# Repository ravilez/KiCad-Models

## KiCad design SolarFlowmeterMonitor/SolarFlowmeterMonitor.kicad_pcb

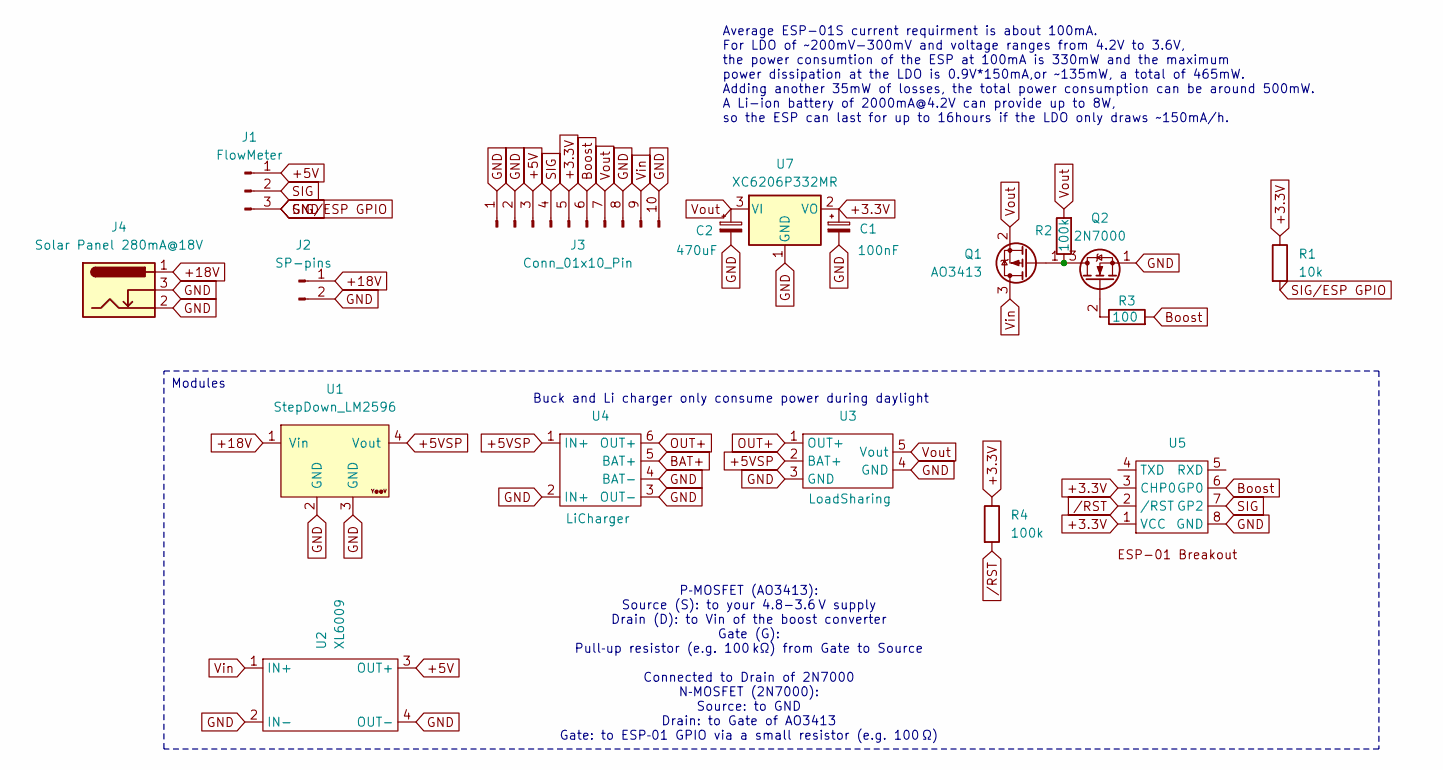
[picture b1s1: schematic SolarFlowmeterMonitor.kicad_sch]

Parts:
C1: 100nF; C_1210_3225Metric_Pad1.33x2.70mm_HandSolder
C2: 470uF; CP_Elec_10x10.5
J1: FlowMeter; PinHeader_1x03_P2.54mm_Vertical
J2: SP-pins; PinSocket_1x02_P2.54mm_Vertical
J3: Conn_01x10_Pin
J4: Solar Panel 280mA@18V; BarrelJack_Horizontal
Q1: AO3413; SOT-23
Q2: 2N7000; TO-92_Inline
R1: 10k; R_1210_3225Metric_Pad1.30x2.65mm_HandSolder
R2, R4: 100k; R_1210_3225Metric_Pad1.30x2.65mm_HandSolder
R3: 100; R_1210_3225Metric_Pad1.30x2.65mm_HandSolder
U1: StepDown_LM2596; YAAJ_DCDC_StepDown_LM2596
U2: XL6009; XL6009_module_TH
U3: LoadSharing; LiPO_SharePower
U4: LiCharger; LiCharger-03962
U5: ESP01-Breakout
U7: XC6206P332MR; SOT-23-3

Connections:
+3.3V: C1.1, J3.5, R1.1, R4.1, U5.1 (VCC), U5.3 (CHP0), U7.2 (VO)
+5V: J1.1, J3.3, U2.3 (OUT+)
+5VSP: U1.4 (Vout), U3.2 (BAT+), U4.1 (IN+)
+18V: J2.1, J4.1, U1.1 (Vin)
BAT+: U4.5 (BAT+)
Boost: J3.6, R3.2, U5.6 (GP0)
GND: C1.2, C2.2, J1.3, J2.2, J3.1, J3.2, J3.8, J3.10, J4.2, J4.3, Q2.1 (S), R1.2, U1.2 (GND), U1.3 (GND), U2.2 (IN-), U2.4 (OUT-), U3.3 (GND), U3.4 (GND), U4.2 (IN+), U4.3 (OUT-), U4.4 (BAT-), U5.8 (GND), U7.1 (GND)
unnamed: Q1.1 (G), Q2.3 (D), R2.1
unnamed: Q2.2 (G), R3.1
OUT+: U3.1 (OUT+), U4.6 (OUT+)
SIG: J1.2, J3.4, U5.7 (GP2)
Vin: J3.9, Q1.3 (D), U2.1 (IN+)
Vout: C2.1, J3.7, Q1.2 (S), R2.2, U3.5 (Vout), U7.3 (VI)
/RST: R4.2, U5.2 (/RST)

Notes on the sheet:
Average ESP-01S current requirment is about 100mA. For LDO of ~200mV-300mV and voltage ranges from 4.2V to 3.6V, the power consumtion of the ESP at 100mA is 330mW and the maximum power dissipation at the LDO is 0.9V*150mA,or ~135mW, a total of 465mW. Adding another 35mW of losses, the total power c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
Buck and Li charger only consume power during daylight
P‑MOSFET (AO3413): Source (S): to your 4.8-3.6 V supply Drain (D): to Vin of the boost converter Gate (G): Pull‑up resistor (e.g. 100 kΩ) from Gate to Source Connected to Drain of 2N7000 N‑MOSFET (2N7000): Source: to GND Drain: to Gate of AO3413 Gate: to ESP‑01 GPIO via a small resistor (e.g. 100 Ω)
Modules

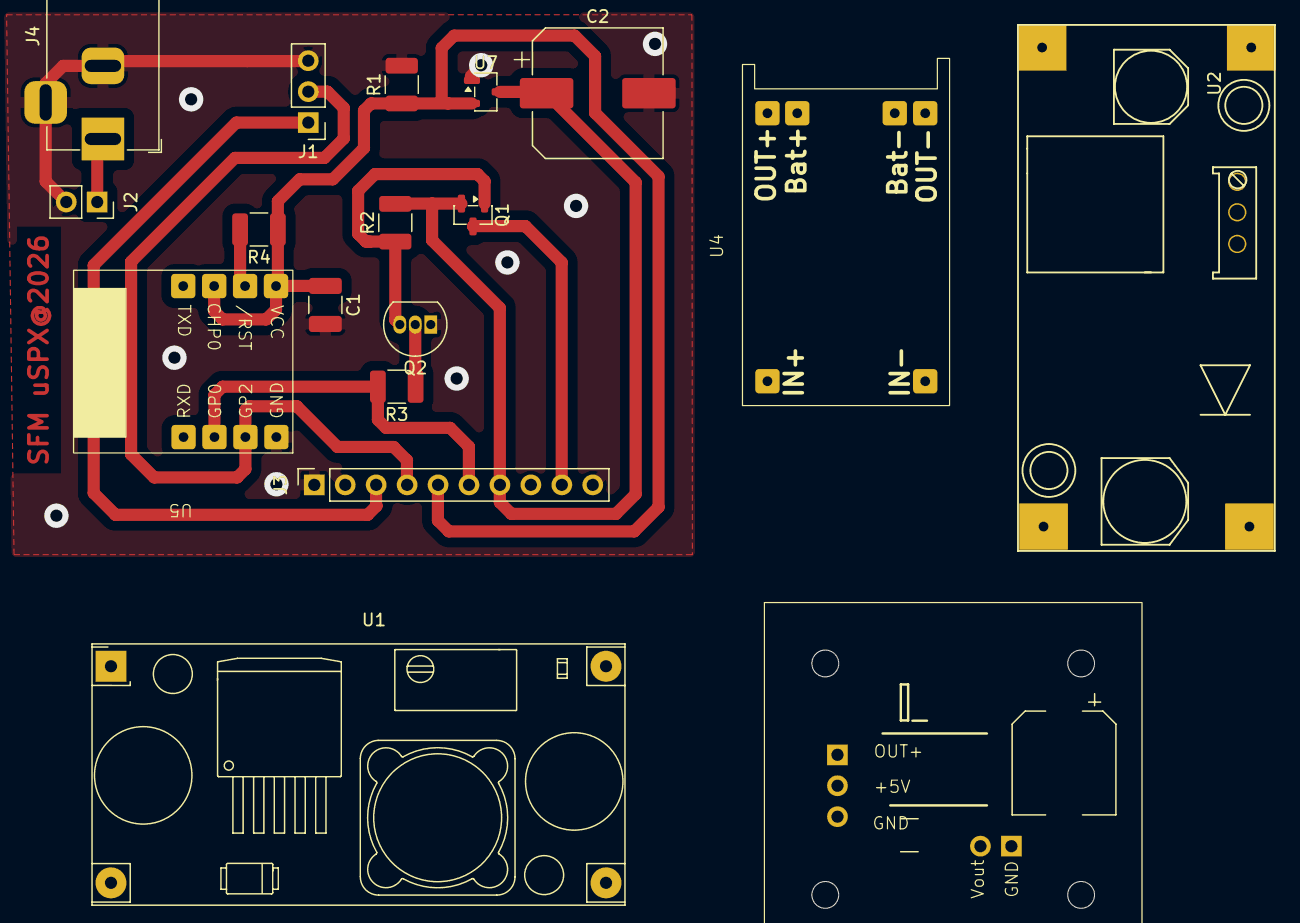
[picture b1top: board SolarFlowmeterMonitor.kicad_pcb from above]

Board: 2 copper layers, 18 parts (0 on the bottom side), 13 nets.

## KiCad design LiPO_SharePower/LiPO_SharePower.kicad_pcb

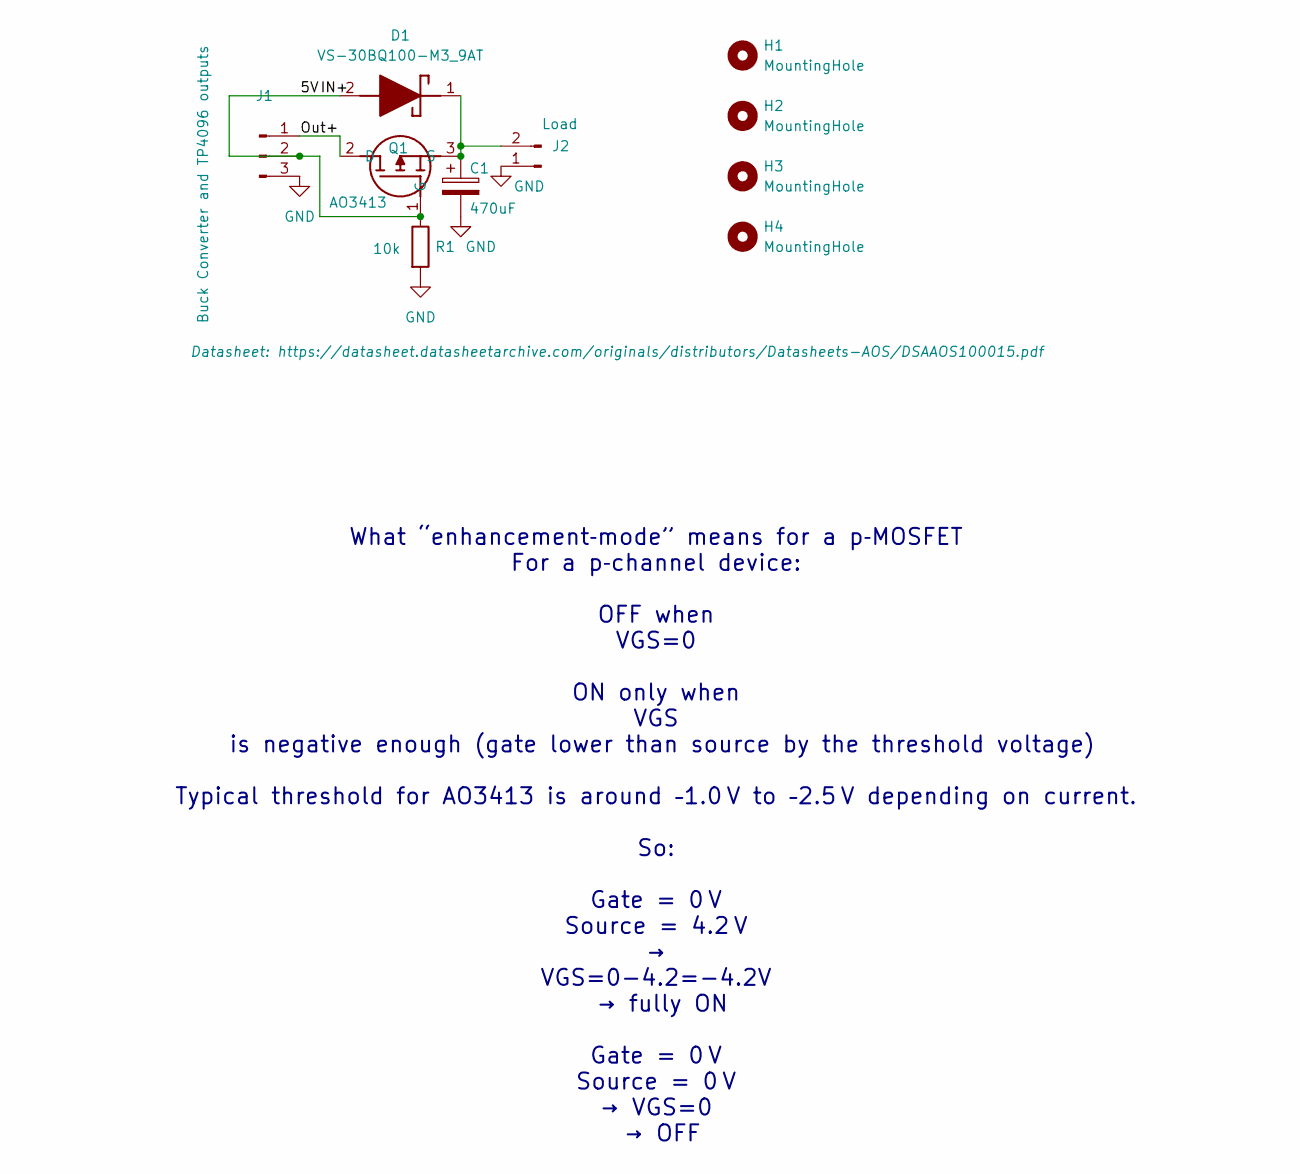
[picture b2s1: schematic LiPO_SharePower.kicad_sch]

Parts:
C1: 470uF; CP_Elec_8x10
D1: VS-30BQ100-M3_9AT; DIOM7959X262N; Manufacturer_Part_Number VS-30BQ100-M3/9AT; Mouser Part Number 78-VS-30BQ100-M39AT
H1, H2, H3, H4: MountingHole; MountingHole_2.2mm_M2
J1: Buck Converter and TP4096 outputs; PinHeader_1x03_P2.54mm_Vertical
J2: Load; PinHeader_1x02_P2.54mm_Vertical
Q1: AO3413; SOT95P280X125-3N; Manufacturer_Part_Number AO3413
R1: 10k; R_1210_3225Metric_Pad1.30x2.65mm_HandSolder

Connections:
/5V: D1.2 (A), J1.2, Q1.1 (G), R1.1
/Out+: J1.1, Q1.2 (D)
GND: C1.2, J1.3, J2.1, R1.2
unnamed: C1.1, D1.1 (K), J2.2, Q1.3 (S)

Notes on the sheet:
What “enhancement‑mode” means for a p‑MOSFET For a p‑channel device: OFF when VGS=0 ON only when VGS is negative enough (gate lower than source by the threshold voltage) Typical threshold for AO3413 is around –1.0 V to –2.5 V depending on current. So: Gate = 0 V Source = 4.2 V → VGS=0−4.2=−4.2V → f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

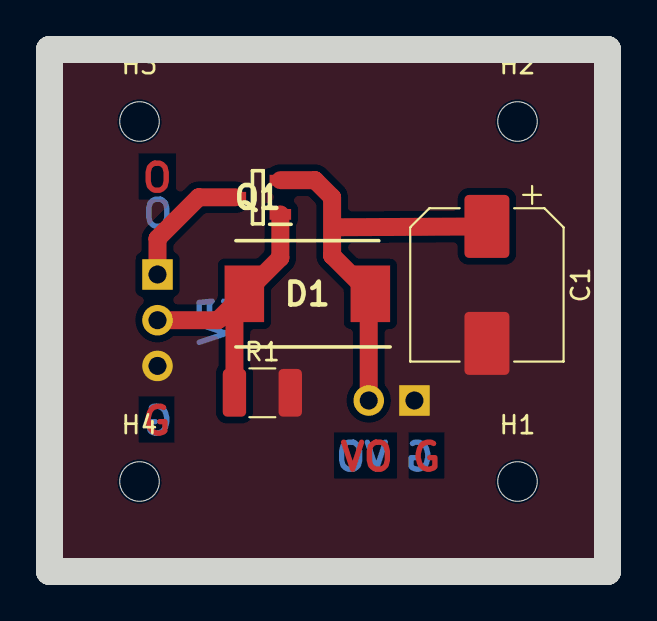
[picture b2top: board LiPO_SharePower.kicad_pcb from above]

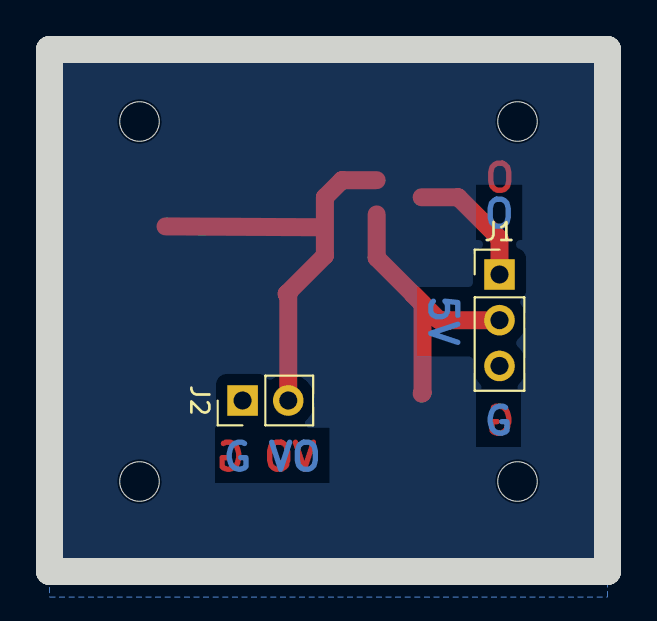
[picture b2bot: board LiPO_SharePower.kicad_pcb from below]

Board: 2 copper layers, 31.0 x 29.0 mm, 10 parts (2 on the bottom side), 4 nets.

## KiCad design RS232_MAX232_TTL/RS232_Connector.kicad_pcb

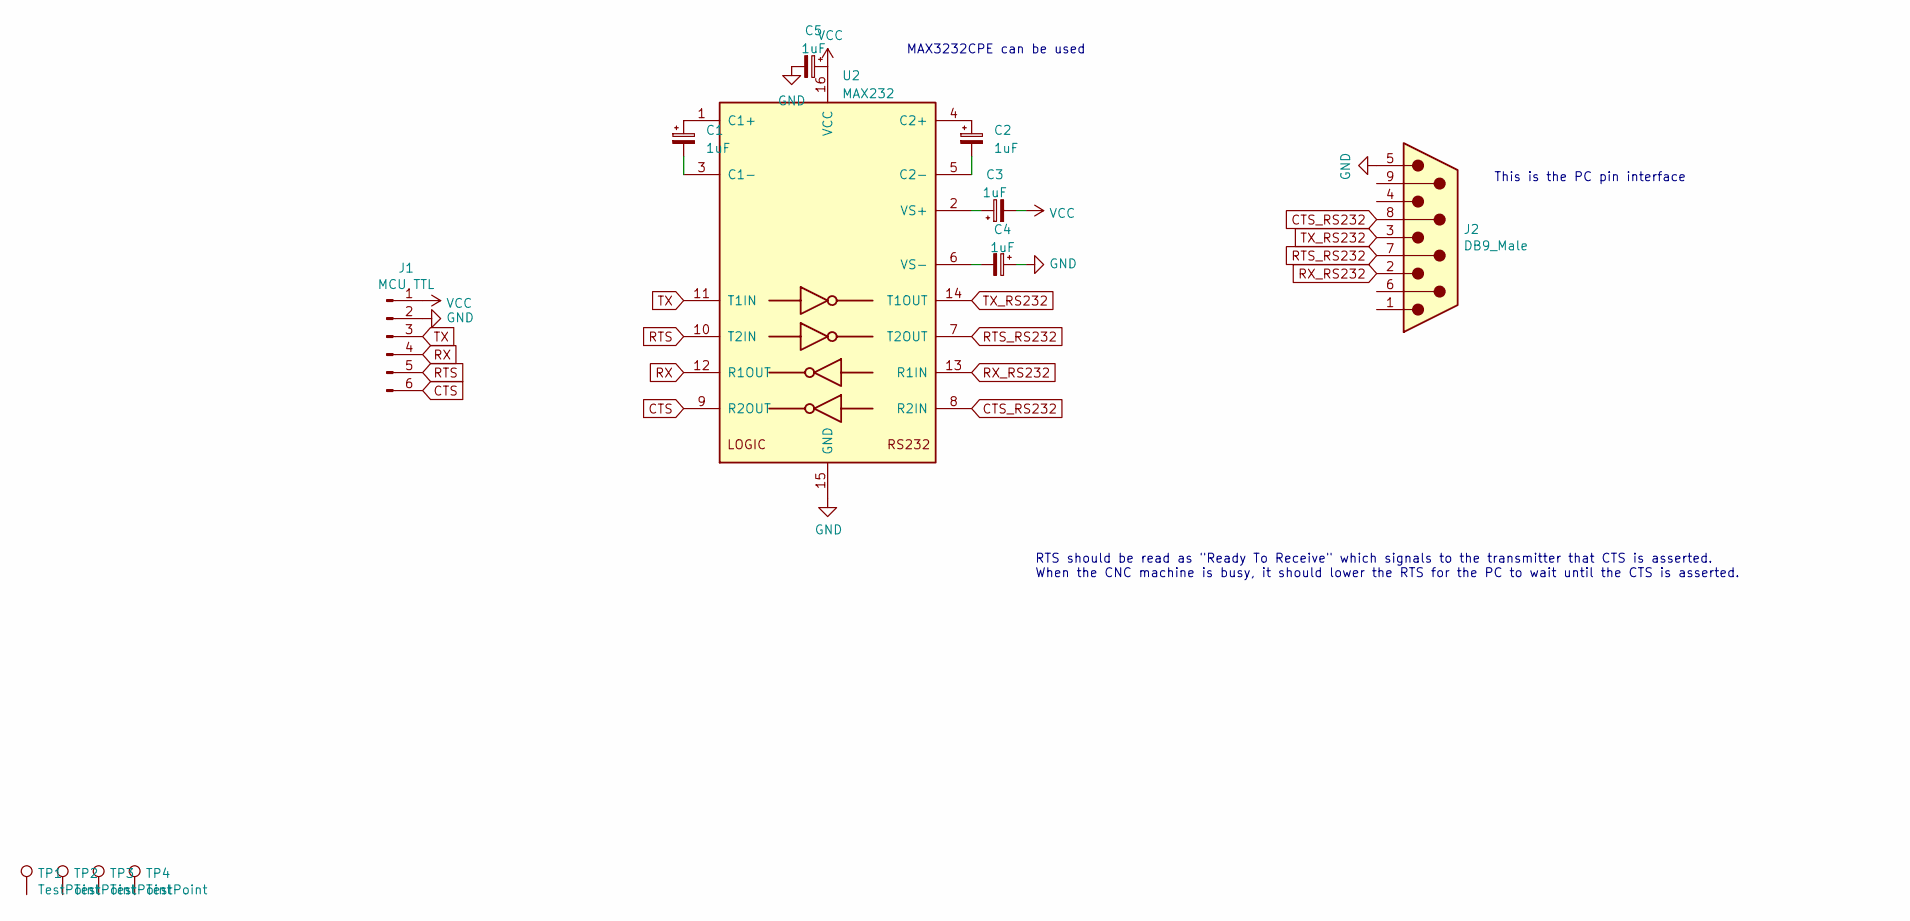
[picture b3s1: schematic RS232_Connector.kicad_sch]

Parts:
C1, C2, C3, C4, C5: 1uF; CP_Radial_D4.0mm_P2.00mm
J1: MCU TTL; PinHeader_1x06_P2.54mm_Vertical
J2: DB9_Male; DSUB-9_Male_Horizontal_P2.77x2.84mm_EdgePinOffset7.70mm_Hou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
TP1, TP2, TP3, TP4: TestPoint; MountingHole_3mm_Pad
U2: MAX232; DIP-16_W7.62mm

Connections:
CTS: J1.6, U2.9 (R2OUT)
CTS_RS232: J2.8, U2.8 (R2IN)
GND: C4.1, C5.2, J1.2, J2.5, U2.15 (GND)
unnamed: C1.1, U2.1 (C1+)
unnamed: C1.2, U2.3 (C1-)
unnamed: C2.1, U2.4 (C2+)
unnamed: C2.2, U2.5 (C2-)
unnamed: C3.1, U2.2 (VS+)
unnamed: C4.2, U2.6 (VS-)
RTS: J1.5, U2.10 (T2IN)
RTS_RS232: J2.7, U2.7 (T2OUT)
RX: J1.4, U2.12 (R1OUT)
RX_RS232: J2.2, U2.13 (R1IN)
TX: J1.3, U2.11 (T1IN)
TX_RS232: J2.3, U2.14 (T1OUT)
VCC: C3.2, C5.1, J1.1, U2.16 (VCC)

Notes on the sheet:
This is the PC pin interface
MAX3232CPE can be used
RTS should be read as "Ready To Receive" which signals to the transmitter that CTS is asserted. When the CNC machine is busy, it should lower the RTS for the PC to wait until the CTS is asserted.

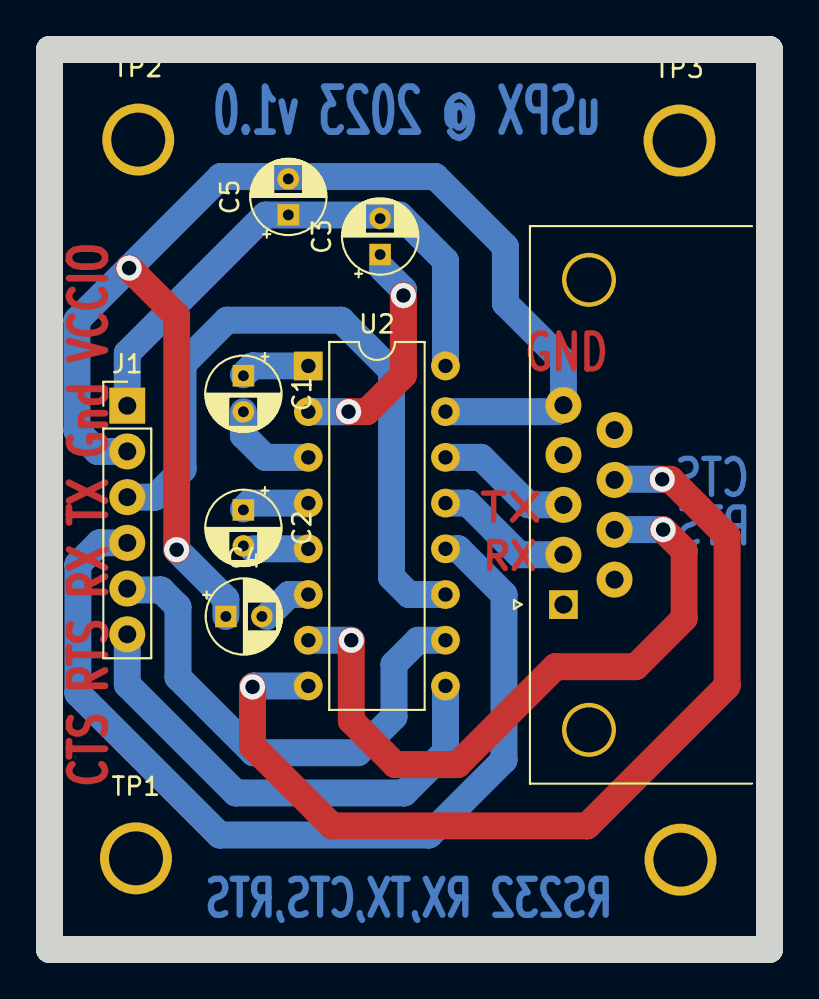
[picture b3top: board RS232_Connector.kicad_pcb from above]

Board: 2 copper layers, 40.0 x 50.0 mm, 12 parts (0 on the bottom side), 16 nets.
